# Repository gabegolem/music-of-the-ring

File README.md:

test
# music-of-the-ring
Personal performance art project utilizing sensor data collected from boxing gloves during a boxing match to generate an digital music accompaniment.

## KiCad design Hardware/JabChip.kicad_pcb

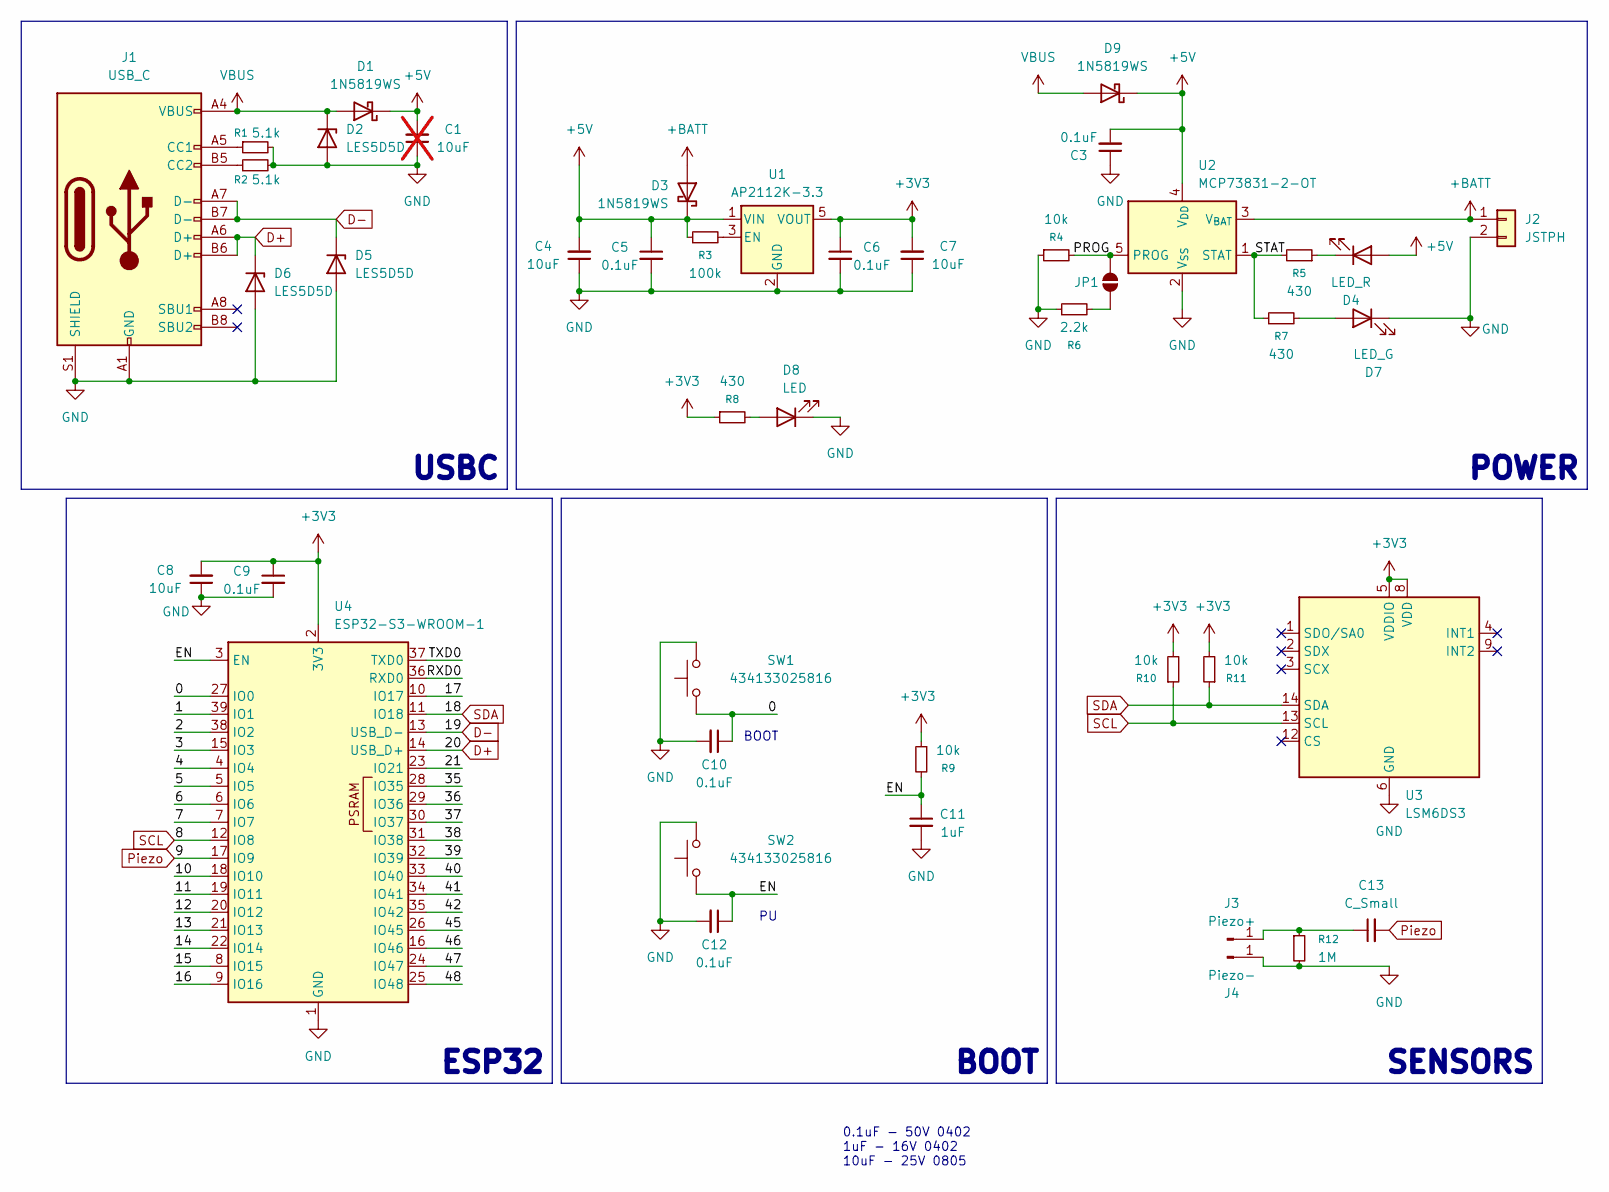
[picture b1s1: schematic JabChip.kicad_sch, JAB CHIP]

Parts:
C1: 10uF; C_0805_2012Metric_Pad1.18x1.45mm_HandSolder; not fitted
C3, C5, C6, C9, C10, C12: 0.1uF; C_0402_1005Metric_Pad0.74x0.62mm_HandSolder
C4, C7, C8: 10uF; C_0402_1005Metric_Pad0.74x0.62mm_HandSolder
C11: 1uF; C_0402_1005Metric_Pad0.74x0.62mm_HandSolder
C13: C_Small; C_0402_1005Metric_Pad0.74x0.62mm_HandSolder
D1, D3, D9: 1N5819WS; D_SOD-323
D2, D5, D6: LES5D5D; D_SOD-523
D4: LED_R; LED_0805_2012Metric_Pad1.15x1.40mm_HandSolder
D7: LED_G; LED_0805_2012Metric_Pad1.15x1.40mm_HandSolder
D8: LED; LED_0805_2012Metric_Pad1.15x1.40mm_HandSolder
J1: USB_C; USB_C_Receptacle_GCT_USB4105-xx-A_16P_TopMnt_Horizontal
J2: JSTPH; JST_PH_B2B-PH-SM4-TB_1x02-1MP_P2.00mm_Vertical
J3: Piezo+; SolderWirePad_1x01_SMD_1x2mm
J4: Piezo-; SolderWirePad_1x01_SMD_1x2mm
JP1: SolderJumper_2_Open; SolderJumper-2_P1.3mm_Open_TrianglePad1.0x1.5mm
R1, R2: 5.1k; R_0402_1005Metric_Pad0.72x0.64mm_HandSolder
R3: 100k; R_0402_1005Metric_Pad0.72x0.64mm_HandSolder
R4, R9, R10, R11: 10k; R_0402_1005Metric_Pad0.72x0.64mm_HandSolder
R5, R7, R8: 430; R_0402_1005Metric_Pad0.72x0.64mm_HandSolder
R6: 2.2k; R_0402_1005Metric_Pad0.72x0.64mm_HandSolder
R12: 1M; R_0402_1005Metric_Pad0.72x0.64mm_HandSolder
SW1, SW2: 434133025816; SW_Push_1P1T_NO_Vertical_Wuerth_434133025816
U1: AP2112K-3.3; SOT-23-5
U2: MCP73831-2-OT; SOT-23-5
U3: LSM6DS3; LGA-14_3x2.5mm_P0.5mm_LayoutBorder3x4y
U4: ESP32-S3-WROOM-1

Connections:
+3V3: C6.1, C7.2, C8.2, C9.1, R8.1, R9.1, R10.2, R11.2, U1.5 (VOUT), U3.5 (VDDIO), U3.8 (VDD), U4.2 (3V3)
+5V: C1.2, C3.2, C4.2, C5.1, D1.1 (K), D3.1 (K), D4.2 (A), D9.1 (K), R3.1, U1.1 (VIN), U2.4 (V_{DD})
+BATT: D3.2 (A), J2.1, U2.3 (V_{BAT})
/0: C10.1, SW1.2, U4.27 (IO0)
/1: U4.39 (IO1)
/2: U4.38 (IO2)
/3: U4.15 (IO3)
/4: U4.4 (IO4)
/5: U4.5 (IO5)
/6: U4.6 (IO6)
/7: U4.7 (IO7)
/10: U4.18 (IO10)
/11: U4.19 (IO11)
/12: U4.20 (IO12)
/13: U4.21 (IO13)
/14: U4.22 (IO14)
/15: U4.8 (IO15)
/16: U4.9 (IO16)
/17: U4.10 (IO17)
/21: U4.23 (IO21)
/35: U4.28 (IO35)
/36: U4.29 (IO36)
/37: U4.30 (IO37)
/38: U4.31 (IO38)
/39: U4.32 (IO39)
/40: U4.33 (IO40)
/41: U4.34 (IO41)
/42: U4.35 (IO42)
/45: U4.26 (IO45)
/46: U4.16 (IO46)
/47: U4.24 (IO47)
/48: U4.25 (IO48)
/EN: C11.1, C12.1, R9.2, SW2.2, U4.3 (EN)
/PROG: JP1.2 (B), R4.2, U2.5 (PROG)
/RXD0: U4.36 (RXD0)
/STAT: R5.2, R7.1, U2.1 (STAT)
/TXD0: U4.37 (TXD0)
D+: D6.1 (K), J1.A6 (D+), J1.B6 (D+), U4.14 (USB_D+)
D-: D5.1 (K), J1.A7 (D-), J1.B7 (D-), U4.13 (USB_D-)
GND: C1.1, C3.1, C4.1, C5.2, C6.2, C7.1, C8.1, C9.2, C10.2, C11.2, C12.2, D2.2 (A), D5.2 (A), D6.2 (A), D7.1 (K), D8.1 (K), J1.A1 (GND), J1.A12 (GND), J1.B1 (GND), J1.B12 (GND), J1.S1 (SHIELD), J2.2, J4.1, R1.2, R2.2, R4.1, R6.1, R12.2, SW1.1, SW2.1, U1.2 (GND), U2.2 (V_{SS}), U3.6 (GND), U3.7 (GND), U4.1 (GND), U4.40 (GND), U4.41 (GND)
unnamed: D4.1 (K), R5.1
unnamed: D7.2 (A), R7.2
unnamed: D8.2 (A), R8.2
unnamed: J1.A5 (CC1), R1.1
unnamed: J1.B5 (CC2), R2.1
unnamed: C13.1, J3.1, R12.1
unnamed: JP1.1 (A), R6.2
unnamed: R3.2, U1.3 (EN)
Piezo: C13.2, U4.17 (IO9)
SCL: R10.1, U3.13 (SCL), U4.12 (IO8)
SDA: R11.1, U3.14 (SDA), U4.11 (IO18)
VBUS: D1.2 (A), D2.1 (K), D9.2 (A), J1.A4 (VBUS), J1.A9 (VBUS), J1.B4 (VBUS), J1.B9 (VBUS)

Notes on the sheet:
USBC
POWER
0.1uF - 50V 0402 1uF - 16V 0402 10uF - 25V 0805
ESP32
BOOT
SENSORS

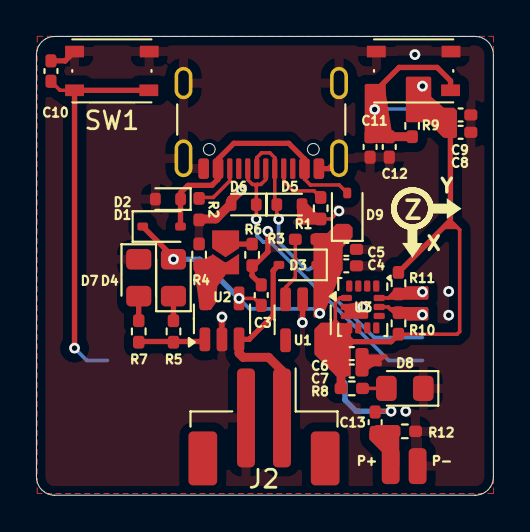
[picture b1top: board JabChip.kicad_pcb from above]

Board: 4 copper layers, 25.4 x 25.5 mm, 43 parts (1 on the bottom side), 22 nets.

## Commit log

2025-11-03 chore: Update .gitignore
2025-11-03 chore: Import JLCPCB design rules
2025-11-03 feat: KiCAD design files
2025-11-03 feat: Gerber files for ordering
2025-11-03 chore: Update gerber files
2025-11-03 style: Clean up schematic
2025-11-03 fix: Reassign piezo from IO3 to IO9 to avoid JTAG debug
2025-11-04 fix: Differential routing
2025-11-04 fix: Silkscreen labels
2025-11-05 test
2025-11-05 Added Bill of Materials
2025-11-20 Successfully transmit imu and piezo reading from esp to laptop over wifi
2025-11-21 Sensor data successfully sent wirelessly, impacts recorded to csv
2025-11-22 !fix: Correct ESD protection diodes and regenerate gerber output files
2025-11-29 Fixed data_reading, centroid.py works, organized directory, added fighter profile directory
2025-11-29 math probably works for identifying punches, test data needs recollected
2025-11-30 Created backlog, added sound files, commented data_reading
2025-11-30 Added to backlog, refactored program files
2025-12-01 Resigned myself to the fact esp now is necessary
2025-12-04 created udp version of data_reading files
2025-12-06 Refactored sound file names
2025-12-06 Save state for named piping attempt
2025-12-06 Pipe save state
2025-12-07 Moved from UDP to OSC
2026-04-07 modelling should work
2026-04-24 Save state cuz I haven't committed in eternity
2026-04-30 everything is bricked
